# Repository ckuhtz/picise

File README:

Picise

Prototype for a time / location accessory for a Raspberry Pi 40-pin GPIO.

Goals:
- high quality time (including pps) and location source
- low cost but not cheap
- all 3.3VDC to keep things simple
- vertical clearance for Pi52's ICE Tower coolers

Status:

Prototype boards ordered.

License:

CERN-OHL-P, see LICENSE file

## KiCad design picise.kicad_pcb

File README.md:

# Picise

Prototype for a time / location accessory for a Raspberry Pi 40-pin GPIO.

## Goals:

- high quality time (including pps) and location source
- low cost but not cheap
- all 3.3VDC to keep things simple
- clearance for Pi52's ICE Tower coolers

Vertical GPIO riser with 
- HAT EEPROM, 
- GNSS, 
- GNSS battery backup, 
- indicators for power and GNSS fix,
- 3.3VDC fan header.

## BOM:

[Digikey](https://www.digikey.com/short/rnq4tnz8)

## Status:

**2022-11-25: rev2 design in progress.**

**2022-11-24: rev1 assembled, working (click on video below). Planning rev2 improvements.**

### PCB:

<p>

### Video:

**2022-11-01: rev1 prototype boards received, pending assembly.**

<p>

Library not published at this time.  Can't remember what has which licensing where I used stuff from vendors.

## License:

CC BY-SA 4.0, see [LICENSE](LICENSE) file.

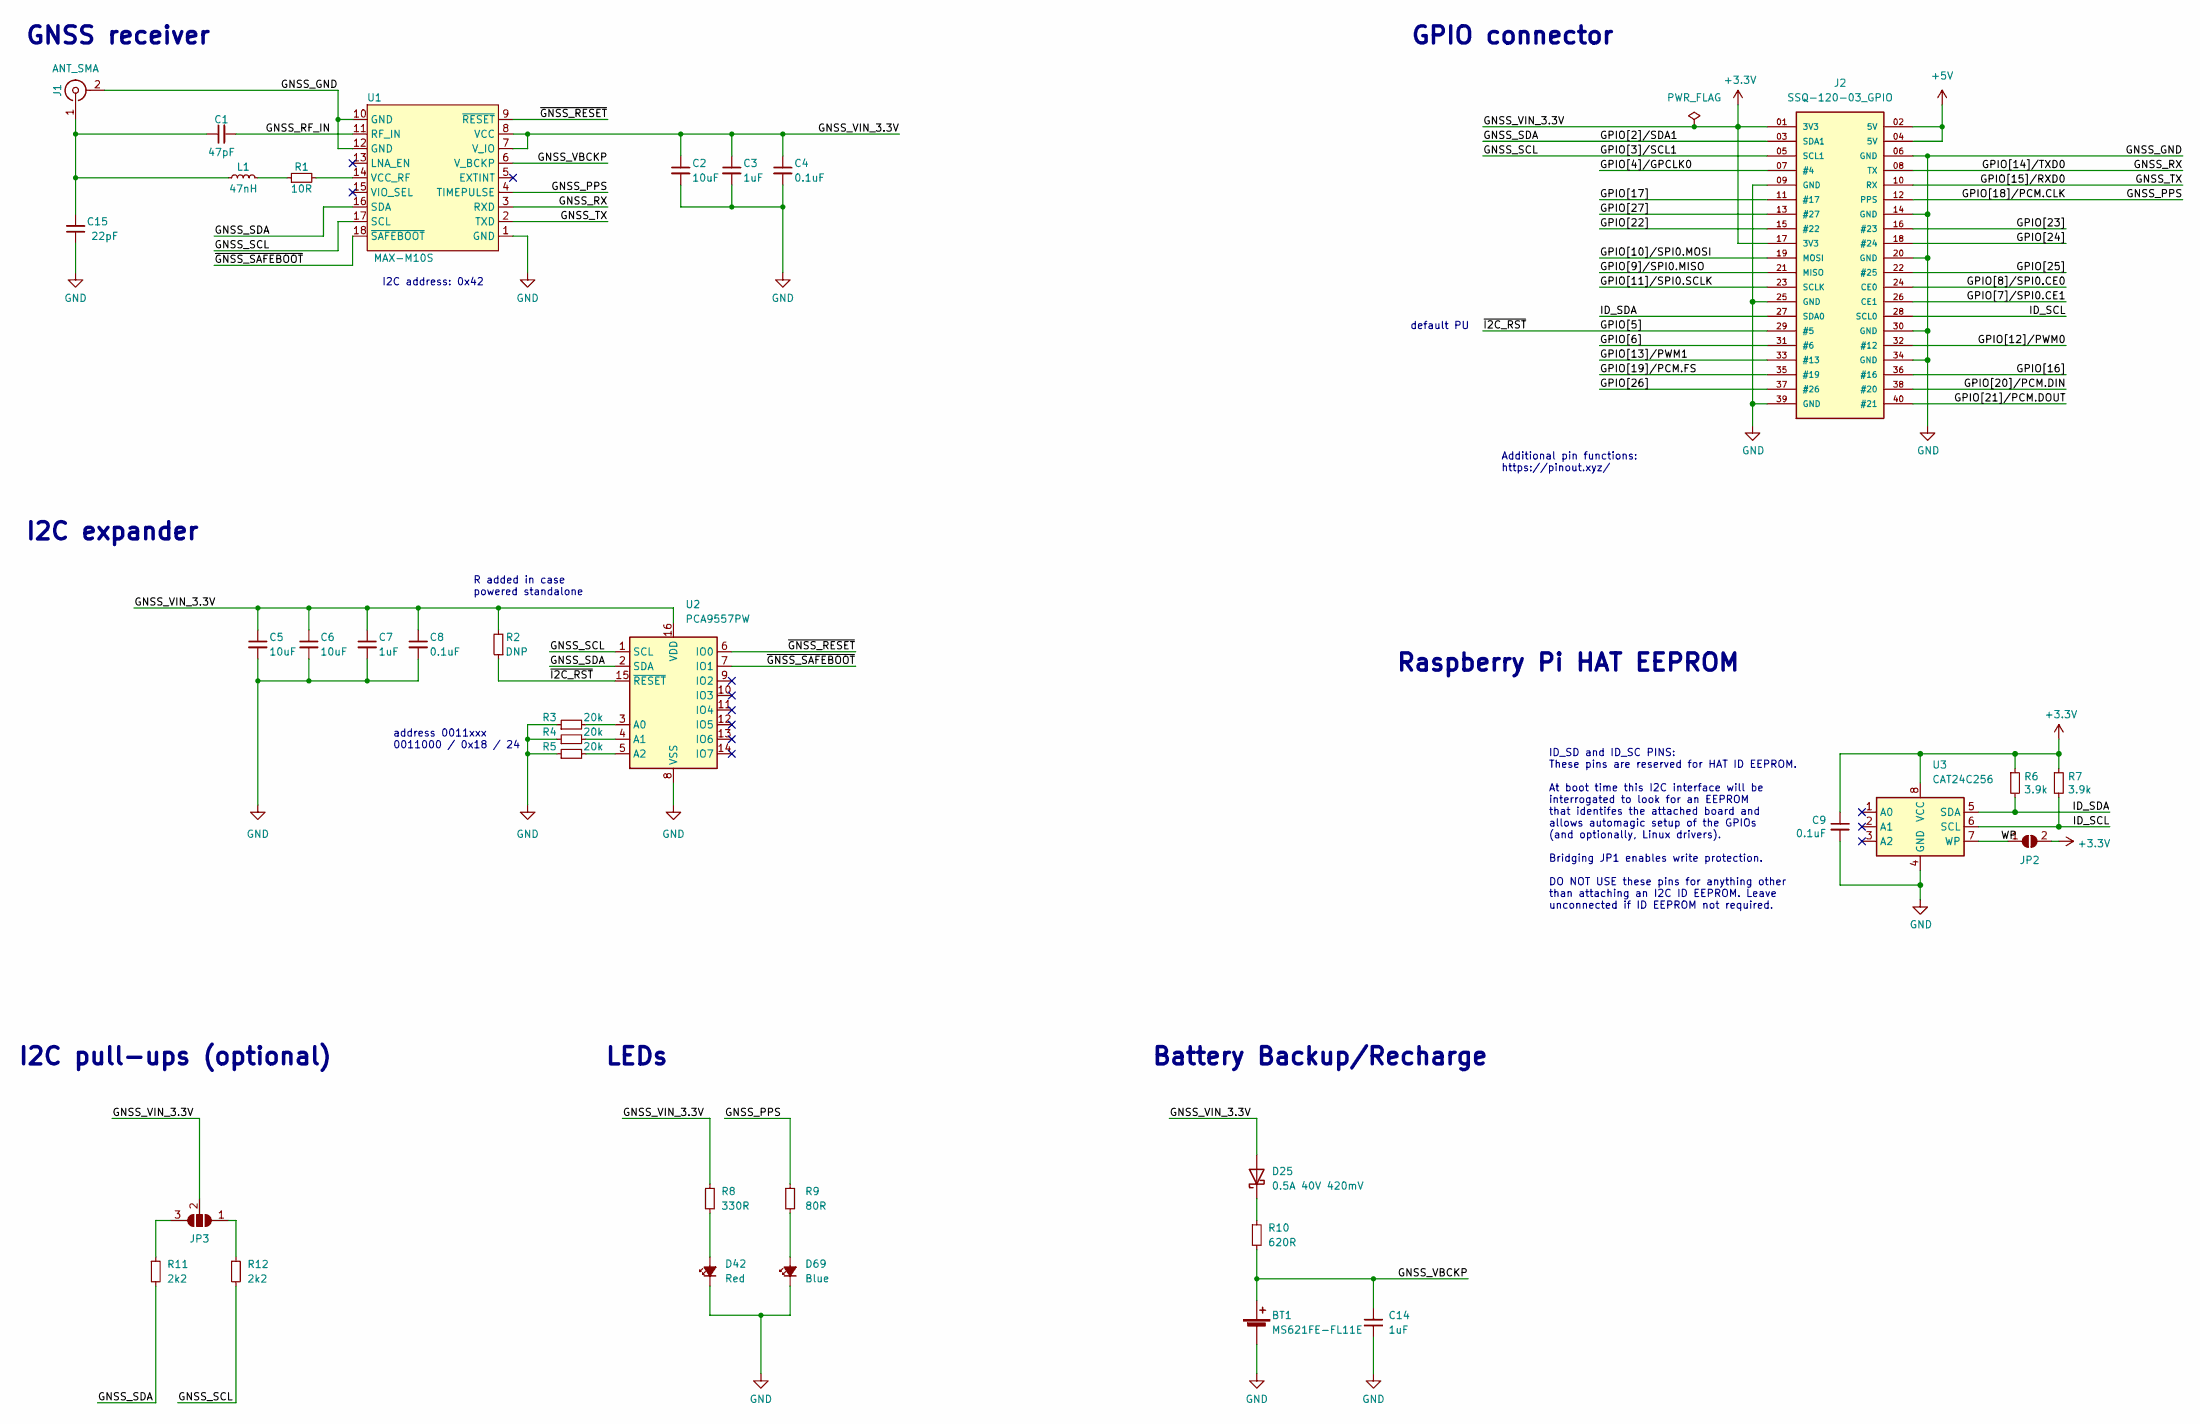
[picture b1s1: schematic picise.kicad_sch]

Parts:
BT1: MS621FE-FL11E; BAT_MS621FE-FL11E; MPN MS621FE-FL11E; Digikey MS621FE-FL11E
C1: 47pF; C_0603_1608Metric; MPN CL10C470JB8NNNC; JLCPCB C1671
C2, C5, C6: 10uF; C_0603_1608Metric; MPN CL05A106MQ5NUNC; JLCPCB C15525
C3, C7, C14: 1uF; C_0603_1608Metric; MPN CL10A105KB8NNNC; JLCPCB C15849
C4, C8, C9: 0.1uF; C_0603_1608Metric; MPN CC0603KRX7R9BB104; JLCPCB C14663
C15: 22pF; C_0603_1608Metric; MPN CL10C470JB8NNNC; JLCPCB C1671
D25: 0.5A 40V 420mV; D_0603_1608Metric; MPN SD0603S040S0R2; JLCPCB C143772
D42: Red; D_0603_1608Metric; MPN LTST-C191KRKT; JLCPCB C125099
D69: Blue; D_0603_1608Metric; MPN 19-217/BHC-ZL1M2RY/3T; JLCPCB C72041
J1: ANT_SMA; SAMTEC_SMA-J-P-H-ST-EM1; MPN SMA-J-P-H-ST-EM1; Digikey SMA-J-P-H-ST-EM1
J2: SSQ-120-03_GPIO; SAMTEC_SSQ-120-03-G-D_Pi; MPN SSQ-120-03-G-D; Digikey SSQ-120-03-G-D
JP2: ID_WP; SolderJumper-2_P1.3mm_Open_RoundedPad1.0x1.5mm
JP3: SolderJumper_3_Open; SolderJumper-3_P1.3mm_Open_RoundedPad1.0x1.5mm
L1: 47nH; L_0603_1608Metric; MPN LQW18AN47NG00D; JLCPCB C98076
R1: 10R; R_0603_1608Metric; MPN 0603WAF100JT5E; JLCPCB C22859
R2: DNP; R_0805_2012Metric_Pad1.20x1.40mm_HandSolder
R3, R4, R5: 20k; R_0603_1608Metric; MPN 0603WAF2002T5E; JLCPCB C4184
R6, R7: 3.9k; R_0603_1608Metric; MPN 0603WAF3901T5E; JLCPCB C23018
R8: 330R; R_0603_1608Metric; MPN 0603WAF3300T5E; JLCPCB C23138
R9: 80R; R_0603_1608Metric; MPN 0603WAF806JT5E; JLCPCB C23115
R10: 620R; R_0603_1608Metric; MPN 0603WAF6200T5E; JLCPCB C23220
R11, R12: 2k2; R_0603_1608Metric; MPN 0603WAF2201T5E; JLCPCB C4190
U1: MAX-M10S; MPN MAX-M10S-00B
U2: PCA9557PW; TSSOP-16_4.4x5mm_P0.65mm; MPN PCA9557PW; JLCPCB C141380
U3: CAT24C256; SOIC-8_3.9x4.9mm_P1.27mm; MPN CAT24C256WI-GT3; JLCPCB C79987

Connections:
+3V3: C2.1, C3.1, C4.1, C5.1, C6.1, C7.1, C8.1, C9.1, D25.2 (A), J2.01 (3V3), J2.17 (3V3), JP2.2 (B), JP3.2 (C), R2.2, R6.1, R7.1, R8.1, U1.7 (V_IO), U1.8 (VCC), U2.16 (VDD), U3.8 (VCC)
+5V: J2.02 (5V), J2.04 (5V)
/GNSS_PPS: J2.12 (PPS), R9.1, U1.4 (TIMEPULSE)
/GNSS_RF_IN: C1.2, U1.11 (RF_IN)
/GNSS_RX: J2.08 (TX), U1.3 (RXD)
/GNSS_SCL: J2.05 (SCL1), R12.2, U1.17 (SCL), U2.1 (SCL)
/GNSS_SDA: J2.03 (SDA1), R11.2, U1.16 (SDA), U2.2 (SDA)
/GNSS_TX: J2.10 (RX), U1.2 (TXD)
/GNSS_VBCKP: BT1.+, C14.1, R10.2, U1.6 (V_BCKP)
/GPIO[4]/GPCLK0: J2.07 (#4)
/GPIO[5]: J2.29 (#5), R2.1, U2.15 (~RESET)
/GPIO[6]: J2.31 (#6)
/GPIO[7]/SPI0.CE1: J2.26 (CE1)
/GPIO[8]/SPI0.CE0: J2.24 (CE0)
/GPIO[9]/SPI0.MISO: J2.21 (MISO)
/GPIO[10]/SPI0.MOSI: J2.19 (MOSI)
/GPIO[11]/SPI0.SCLK: J2.23 (SCLK)
/GPIO[12]/PWM0: J2.32 (#12)
/GPIO[13]/PWM1: J2.33 (#13)
/GPIO[16]: J2.36 (#16)
/GPIO[17]: J2.11 (#17)
/GPIO[19]/PCM.FS: J2.35 (#19)
/GPIO[20]/PCM.DIN: J2.38 (#20)
/GPIO[21]/PCM.DOUT: J2.40 (#21)
/GPIO[22]: J2.15 (#22)
/GPIO[23]: J2.16 (#23)
/GPIO[24]: J2.18 (#24)
/GPIO[25]: J2.22 (#25)
/GPIO[26]: J2.37 (#26)
/GPIO[27]: J2.13 (#27)
/ID_SCL: J2.28 (SCL0), R7.2, U3.6 (SCL)
/ID_SDA: J2.27 (SDA0), R6.2, U3.5 (SDA)
/WP: JP2.1 (A), U3.7 (WP)
/~GNSS_RESET: U1.9 (~RESET), U2.6 (IO0)
/~GNSS_SAFEBOOT: U1.18 (~SAFEBOOT), U2.7 (IO1)
GND: BT1.-, C2.2, C3.2, C4.2, C5.2, C6.2, C7.2, C8.2, C9.2, C14.2, C15.1, D42.1 (K), D69.1 (K), J1.2, J2.06 (GND), J2.09 (GND), J2.14 (GND), J2.20 (GND), J2.25 (GND), J2.30 (GND), J2.34 (GND), J2.39 (GND), R3.1, R4.1, R5.1, U1.1 (GND), U1.10 (GND), U1.12 (GND), U2.8 (VSS), U3.4 (GND)
unnamed: C1.1, C15.2, J1.1, L1.1
unnamed: D25.1 (K), R10.1
unnamed: D42.2 (A), R8.2
unnamed: D69.2 (A), R9.2
unnamed: JP3.1 (A), R12.1
unnamed: JP3.3 (B), R11.1
unnamed: L1.2, R1.1
unnamed: R1.2, U1.14 (VCC_RF)
unnamed: R3.2, U2.3 (A0)
unnamed: R4.2, U2.4 (A1)
unnamed: R5.2, U2.5 (A2)

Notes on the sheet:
Raspberry Pi HAT EEPROM
Additional pin functions: https://pinout.xyz/
GNSS receiver
Battery Backup/Recharge
ID_SD and ID_SC PINS: These pins are reserved for HAT ID EEPROM. At boot time this I2C interface will be interrogated to look for an EEPROM that identifes the attached board and allows automagic setup of the GPIOs (and optionally, Linux drivers). Bridging JP1 enables write protection. DO NOT USE th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
R added in case powered standalone
I2C expander
I2C address: 0x42
address 0011xxx 0011000 / 0x18 / 24
default PU
GPIO connector
LEDs
I2C pull-ups (optional)

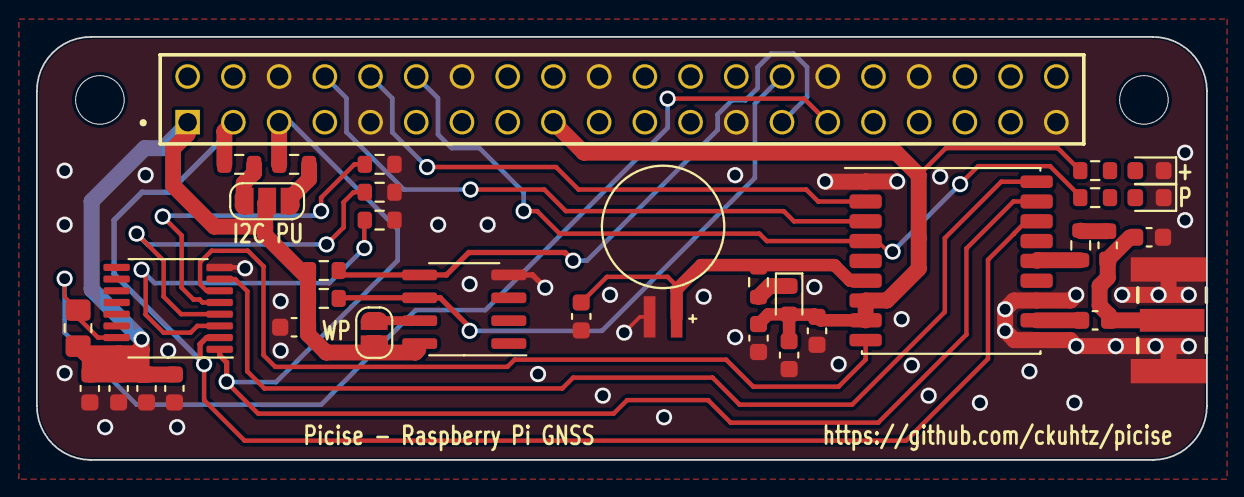
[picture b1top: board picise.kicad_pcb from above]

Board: 2 copper layers, 65.0 x 23.5 mm, 37 parts (0 on the bottom side), 27 nets.

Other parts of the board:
MH1, MH2: MountingHole_2.7mm_M2.5

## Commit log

2022-10-25 cropped renders
2022-10-25 updated
    Sparkfun uses CC SA 4.0, which requires these license terms to be passed on. Rather than try to figure out if CC SA 4.0 and CERN OHL-P are compatible, I'm changing the licensing ahead of making this 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
2022-10-25 moving README to markdown
2022-10-25 Update README.md
    formatting, some content
2022-10-31 Update README.md
    Added Digikey BOM
2022-10-31 added BOM
2022-10-31 BOM tweak
    3-pin to account for left pin 1
2022-10-31 updated digikey bom link
2022-11-24 rev2 prep
2022-11-24 pcb pics
2022-11-24 resized pic
2022-11-25 rev2 board prep
2022-11-26 rev2 draft routed
2022-11-26 rev2 artifacts
2022-11-26 tweaks
2022-11-27 more rev2 work
2022-11-27 updated renders
2022-11-27 updated origin
2022-11-27 fab outputs

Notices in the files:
picise.kicad_pcb:
Copyright (C) 2022 Christian Kuhtz
